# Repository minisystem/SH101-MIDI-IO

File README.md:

# SH101 MIDI IO
PCB assembly for TRS-DIN MIDI connections to SH-101

## Overview
[Tubbutec](https://tubbutec.de/sh-1oh1/) make an amazing upgrade kit for the Roland SH-101 that replaces the original CPU, adding MIDI, some new modulation sources, and an enhanced sequencer and arpeggiator. The kit comes with a pair of MIDI jacks that can be mounted by drilling holes in the enclosure, or concealed in the battery compartment. This respository contains the design files to build a TRS adapter board to replace the SH-101's MODULATION GRIP PCB, which allows the use of Type A TRS-MIDI cables. The MIDI IN uses the 3.5 MM jack and the MIDI OUT uses the 2.5 MM jack. To get the jacks to the right height, a PCB sandwich is required with 1.5 MM spacers. I used SMT M3 spacers, but a regular PCB spacer of the right height should work as well. There's enough room in the enclsoure to leave the original MODULATION GRIP PCB, so it does not need to be disconnected or removed. The jack PCB needs to be 1 MM thick, and the spacer PCB needs to be 1.6 MM thick.

The project was designed in Kicad 6.0. The BOM and pos files for PCBA of the modulation grip spacer PCB with SMT spacers have been formatted for the JLC PCBA service.

## BOM

| Part Ref | Description | Part No |
| -------- | ----------- | ------- |
| J1 | 3.5 MM JACK | CUI SJ1-3523N |
| J2 | 2.5 MM JACK | CUI SJ1-2503A |
| J3 | 5 POS HEADER | 0.100" RIGHT ANGLE |
| SM1-4 | 1.5 MM M3 SPACER | SMTSO3015CTJ |

You'll also need a Type A 3.5 MM TRS MIDI cable and a 2.5 MM TRS MIDI cable if you want access to MIDI OUT data. The 2.5 MM TRS to MIDI cable isn't as widely availabe, but is used by a lot of IK Multimedia iRig series products.

## PCBs

The PCB fabrication files are in the [gerbers](/gerbers/) folder. _SH101_IO.zip_ contains the gerber files for the 1 MM thick jack board and _SH101_MOD_GRIP_BOARD.zip_ contains the gerbers for the 1.6 MM modulation grip spacer board. 

## Assembly

Once assembled, the PCB sandwich slides into guide slots of the plastic enclosure. Tape the original modulation grip jack board to the side of the enclosure. Use a 5 conductor connector assembly, crimp contacts, 0.100" pitch (TE 5-103975-4 or equivalent). Refer to the schematic and PCB markings for wiring order.

The Type A TRS wiring is as follows:

MIDI 4 (source) > RING

MIDI 2 (shield) > SLEEVE

MIDI 5 (sink) > TIP

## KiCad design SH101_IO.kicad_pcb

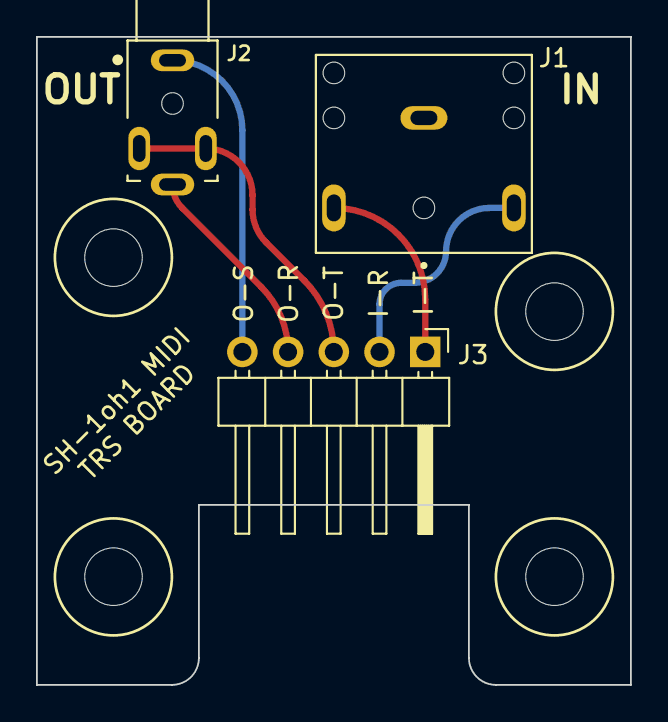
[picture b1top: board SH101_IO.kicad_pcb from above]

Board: 2 copper layers, 33.0 x 36.0 mm, 3 parts (0 on the bottom side), 5 nets.

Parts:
J1: AudioJack3; CUI_SJ1-3523N
J2: AudioJack3; CUI_SJ1-2503A
J3: Conn_01x05_Male; PinHeader_1x05_P2.54mm_Horizontal

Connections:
unnamed: J1.R, J3.2
unnamed: J1.T, J3.1
unnamed: J2.R, J3.4
unnamed: J2.S, J3.5
unnamed: J2.T, J3.3

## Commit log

2023-12-16 added pcb photo
2023-12-16 markup fix
2023-12-16 removed backup folder
2023-12-16 cleanup 3d files
2023-12-16 added drawing views
2023-12-16 updated ortho view
